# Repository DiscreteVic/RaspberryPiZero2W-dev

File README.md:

# RaspberryPiZero2W-dev
Bare-metal develop environment over Raspberry Pi Zero 2 W

Following tutorial from: https://metebalci.com/blog/bare-metal-raspberry-pi-3b-jtag/

## HOW TO BUILD THE INITIAL MINIMAL SETUP ON THE BOARD

1. Format SD card with the common way (Raspberry Pi OS) recommended by Raspberry Pi Foundation.
2. Remove all partitions except Boot partition.
3. Clean the Boot partition.
4. Add the env/minimal_setup files to the Boot partition.

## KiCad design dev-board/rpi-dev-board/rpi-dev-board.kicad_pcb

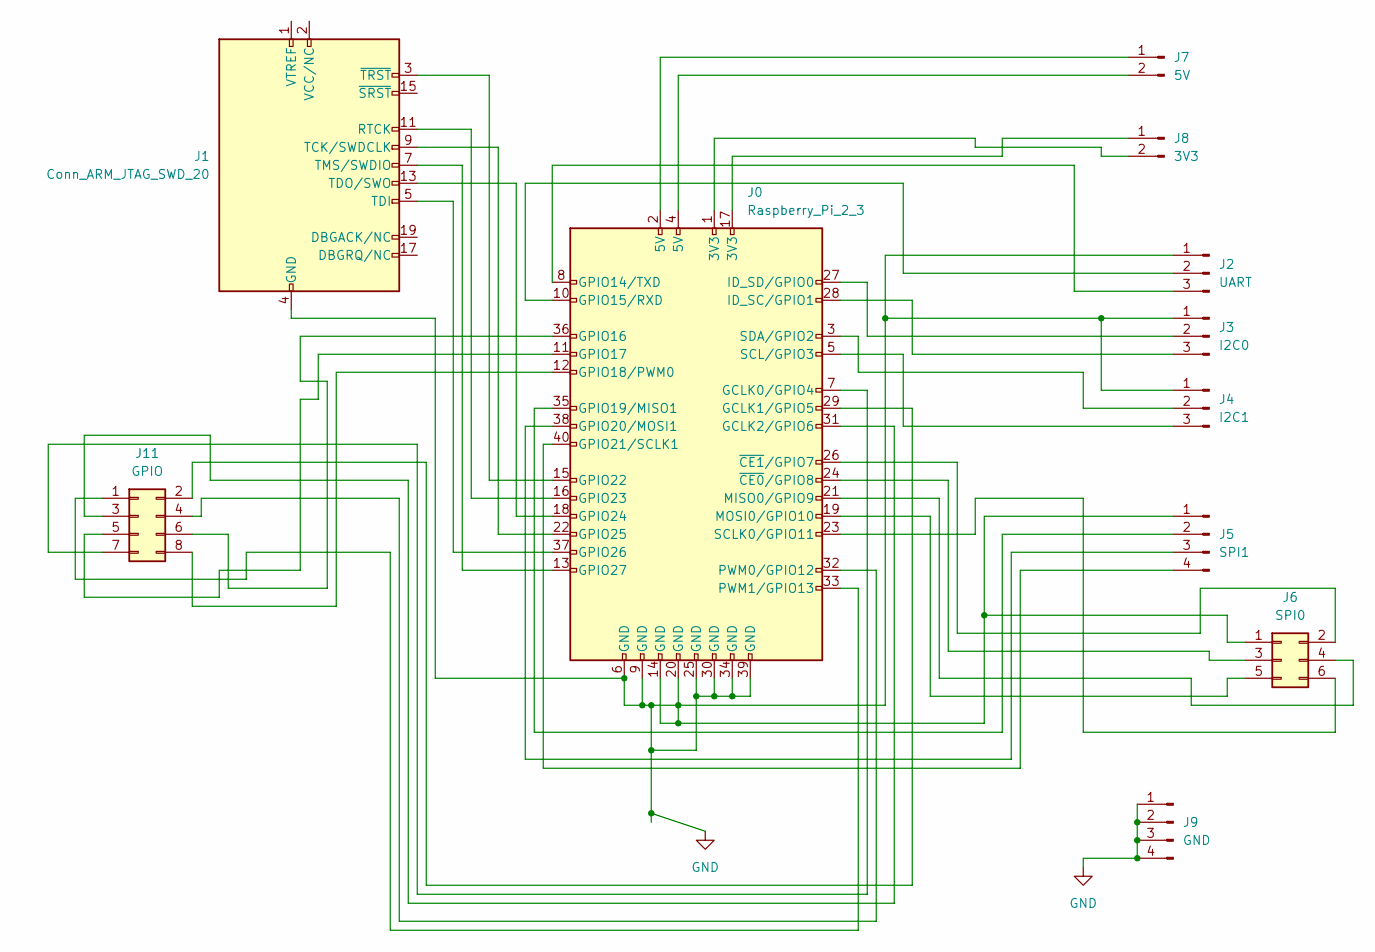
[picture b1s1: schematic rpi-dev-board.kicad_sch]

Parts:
J0: Raspberry_Pi_2_3; PinHeader_2x20_P2.54mm_Vertical
J1: Conn_ARM_JTAG_SWD_20; PinHeader_2x10_P2.54mm_Vertical
J2: UART; PinHeader_1x03_P2.54mm_Vertical
J3: I2C0; PinHeader_1x03_P2.54mm_Vertical
J4: I2C1; PinHeader_1x03_P2.54mm_Vertical
J5: SPI1; PinHeader_1x04_P2.54mm_Vertical
J6: SPI0; PinHeader_2x03_P2.54mm_Vertical
J7: 5V; PinHeader_1x02_P2.54mm_Vertical
J8: 3V3; PinHeader_1x02_P2.54mm_Vertical
J9: GND; PinHeader_1x04_P2.54mm_Vertical
J11: GPIO; PinHeader_2x04_P2.54mm_Vertical

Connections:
unnamed: J0.1 (3V3), J8.2
unnamed: J0.2 (5V), J7.1
unnamed: J0.3 (SDA/GPIO2), J4.2
unnamed: J0.4 (5V), J7.2
unnamed: J0.5 (SCL/GPIO3), J4.3
unnamed: J0.7 (GCLK0/GPIO4), J11.7
unnamed: J0.8 (GPIO14/TXD), J2.3
unnamed: J0.10 (GPIO15/RXD), J2.2
unnamed: J0.11 (GPIO17), J11.5
unnamed: J0.12 (GPIO18/PWM0), J11.8
unnamed: J0.13 (GPIO27), J1.7 (TMS/SWDIO)
unnamed: J0.15 (GPIO22), J1.3 (~TRST)
unnamed: J0.16 (GPIO23), J1.11 (RTCK)
unnamed: J0.17 (3V3), J8.1
unnamed: J0.18 (GPIO24), J1.13 (TDO/SWO)
unnamed: J0.19 (MOSI0/GPIO10), J6.5
unnamed: J0.21 (MISO0/GPIO9), J6.4
unnamed: J0.22 (GPIO25), J1.9 (TCK/SWDCLK)
unnamed: J0.23 (SCLK0/GPIO11), J6.6
unnamed: J0.24 (~CE0/GPIO8), J6.3
unnamed: J0.26 (~CE1/GPIO7), J6.2
unnamed: J0.27 (ID_SD/GPIO0), J3.2
unnamed: J0.28 (ID_SC/GPIO1), J3.3
unnamed: J0.31 (GCLK2/GPIO6), J11.3
unnamed: J0.32 (PWM0/GPIO12), J11.4
unnamed: J0.33 (PWM1/GPIO13), J11.1
unnamed: J0.35 (GPIO19/MISO1), J5.2
unnamed: J0.36 (GPIO16), J11.6
unnamed: J0.37 (GPIO26), J1.5 (TDI)
unnamed: J0.38 (GPIO20/MOSI1), J5.3
unnamed: J0.40 (GPIO21/SCLK1), J5.4
unnamed: J0.29 (GCLK1/GPIO5), J11.2

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
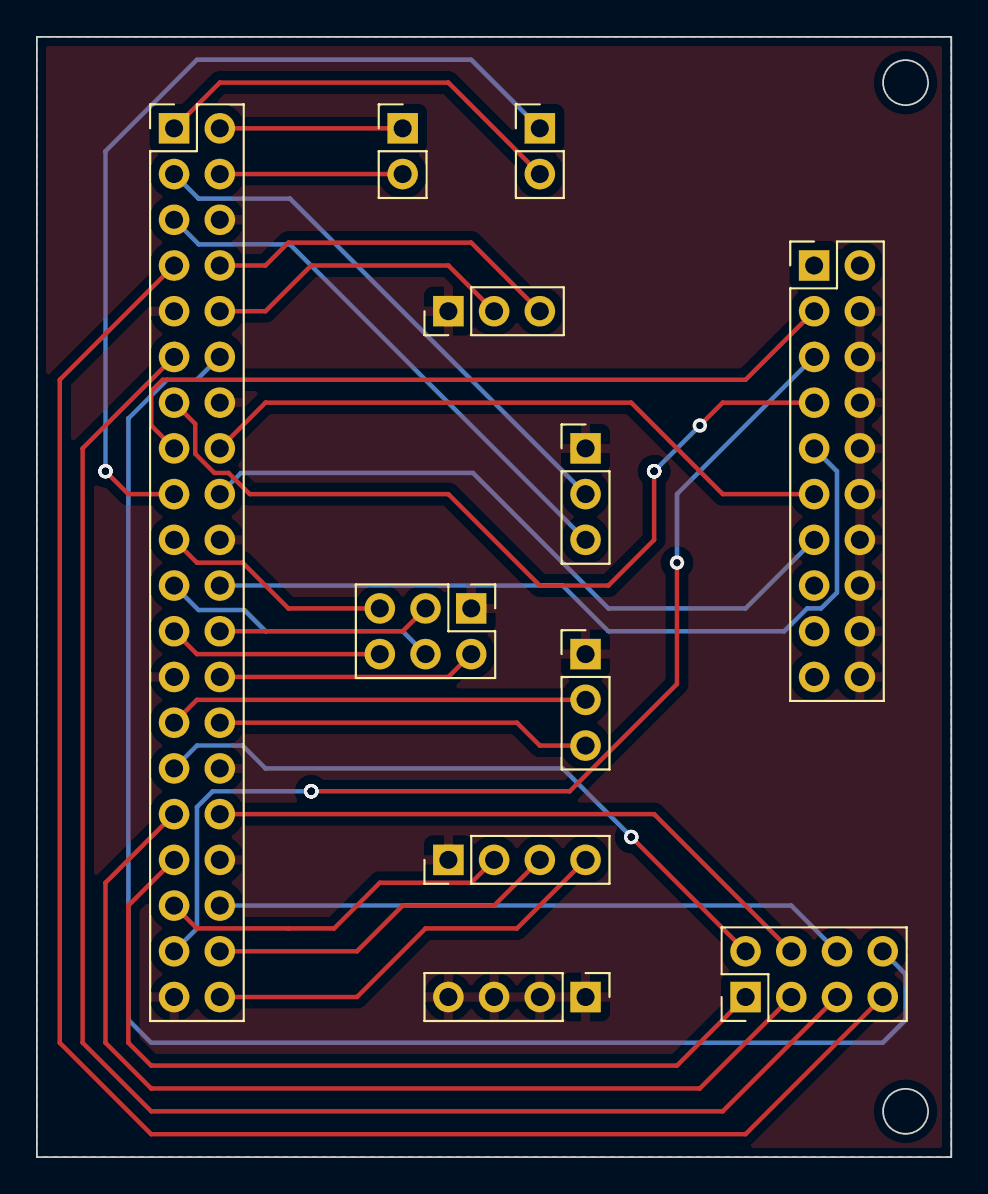
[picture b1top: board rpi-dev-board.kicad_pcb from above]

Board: 2 copper layers, 50.8 x 62.2 mm, 11 parts (0 on the bottom side), 33 nets.

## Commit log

2022-11-07 Added openocd server and gdb client
2022-11-07 Added minimal setup, 64 bits version
2022-11-07 Fixed minor error
2022-11-08 Added 32bits enviroment
2022-11-09 Running code with big errors
2022-11-09 Uploaded C code with linker script, initial running properly
2022-11-10 UART RUNNING!
2022-11-10 Developed BCM2835 library NOT RUNNING
2022-11-10 UART running, sp initial value hard coded
2022-12-10 Added GPIO functions, tested and running
2022-12-13 Added soft wait_ms function
2022-12-18 Designed Dev Board PCB with DD logo
2022-12-28 Added UART functions to print Register and array
2022-12-29 Added hard wait functions and repaired GPIO config function
2023-01-02 Basic functions to HDMI Support
2023-01-03 Added Video functions to BCM2835 Lib
2023-06-06 Added dockered enviroment
2023-06-07 printing with HDMI an image
2023-06-18 DMA example working
2023-06-18 video HDMI working with DMA, image printed
2023-07-10 Files organized, minor errors
2023-07-11 DMA library finished and running Video
2023-07-11 minor changes, video errors remains
